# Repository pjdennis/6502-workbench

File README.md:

# 6502 workbench

Homebrew 6502 single-board computers and the software written for them: board firmware and peripheral drivers, self-hosting assemblers, a vi-like editor, a Prog8 compiler that compiles itself on the target, and a board-accurate emulator. It has grown since 2020. [`docs/history.md`](docs/history.md) tells the story and shows how to build each era.

This repository continues `pjdennis/6502-experiments`, reorganized in 2026-09 with its full history. Every commit of every old branch is here: on `main`, or, for work that was never merged, reachable from an `archive/<branch>` tag. There is one such tag for each old branch, recording where it pointed.

## Map

| Directory | What's there |
|---|---|
| [`hardware/`](hardware/) | The boards: **Wendy** (v1, 2020), **Michael** (v2, 2021) and **Wendy 2** (2022, now revision c). PLD equations, pin notes, revision history, and the Arduino monitor used with Michael. |
| [`firmware/`](firmware/) | Everything assembled with vasm for the real boards: shared libraries (`lib/`), per-board config and loaders (`boards/`), programs (`programs/`), fonts. |
| [`emulator/`](emulator/) | C emulator. `nmos-default` is a host-stub machine for the assemblers and editor. `wendy2c` models Wendy 2 rev c chip by chip (PLD, VIA, LCD, banked RAM), with web, audio and serial-link front ends. |
| [`asm/`](asm/) | The assembler, bootstrapped from nothing: `00/asm.c`, then stages `01`…`17`, each built by the one before. `17/` is the live assembler. |
| [`editor/`](editor/) | A vi-like text editor written in the assembler's dialect and built by stage 17. Runs in the emulator's terminal and on the Michael board. |
| [`prog8/`](prog8/) | Prog8 compiler work: host compiler `p8c`, `tinyp8`, the self-hosting `p1`, and custom upstream prog8c targets for Wendy 2. |
| [`lathe/`](lathe/) | Lathe, a high-level language and compiler designed to compile on a 6502. Design documents only so far. |
| [`tools/`](tools/) | Host-side tools: serial upload (`upload/`), webcam LCD OCR (`lcd-ocr/`), `makerom.py`, the firmware regression check, `check_all.sh`. |
| [`research/`](research/) | Analyses, e.g. a byte-level breakdown of BBC BASIC IV. |
| [`attic/`](attic/) | Stale, broken or superseded things kept for review, including the first assembler (`asm1/`, 2022–2025). See [`attic/README.md`](attic/README.md). |
| [`docs/`](docs/README.md) | History, the plan behind the 2026 reorganization, and the plans for Michael's ROM and upload format (both done). |

## Quick start

Prerequisites:
- `gcc`, `make` and `python3`
- **vasm** (`vasm6502_oldstyle`, CPU=6502 SYNTAX=oldstyle), on `PATH`. 1.9f to 2.0f all work; CI uses 2.0f from <http://phoenix.owl.de/tags/vasm2_0f.tar.gz>. See `firmware/README.md`.
- Optional: `hexdump`, `64tass`, Java with prog8c 12.1.1, and Python `playwright`. Tests that need a missing tool are skipped.

```bash
make                                   # build the emulator (emulator/emulator.out)
tools/build_all.sh                     # ...or the emulator, assembler and editor (about 30 seconds)
tools/check_all.sh                     # run the test suites, all but the slow prog8 (about 2 minutes)
tools/check_all.sh firmware asm        # ...or just some: firmware asm editor emulator prog8

# Assemble and upload a program to a board over serial
tools/upload/compile_and_upload_wendy2.sh firmware/programs/wendy2/hello_ram_4000_wendy2c.s

# Try Wendy 2 without the hardware
bash emulator/demo_wendy2c.sh --live
```

CI (`.github/workflows/ci.yml`) runs all five `check_all.sh` suites, prog8 included, on every push.

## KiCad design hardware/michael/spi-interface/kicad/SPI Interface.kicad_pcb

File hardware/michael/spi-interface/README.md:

# Michael: the SPI interface in logic chips (2022–2025)

The designs for the interface between Michael's VIA and the SPI display, before the FPGA, kept as found on
2026-10-25 (file dates preserved). The write-up, with the timeline and a review of each design:
[`docs/michael-spi-interface-logic-designs.md`](../../../docs/michael-spi-interface-logic-designs.md).

| Directory | What | Open with |
|---|---|---|
| [`logisim/`](logisim/) | `SPI.circ`, `SPI2.circ`, `SPI3.circ`, `299.circ` (2022-09-13 to 15) | Logisim 2.7 |
| [`digital/`](digital/) | `D-SPI.dig` and its `e-4017.dig`, `D-SPI2.dig`, `shtest.dig` (2022-09-15/16), `D-SPI-WriteOnly.dig` and its Verilog (2024-10-15); `CUPL_D-SPI2/CUPL.PLD` and `test.v`, exported by Digital (2022-09-16); an SVG of each circuit | [Digital](https://github.com/hneemann/Digital) v0.29 |
| [`kicad/`](kicad/) | "Bidirectional SPI interface" rev 0.1 in 74LS chips (2025-10-04): schematic, and a PCB with the parts placed but not routed | KiCad 6 |
| [`gal/`](gal/) | `spi-control.pld` for a GAL20RA10 and a 74HC299 (2025-10-10) and `program-spi.sh`; [`bring-up/`](gal/bring-up/), the GAL20RA10 test designs of 2025-10-04 | GALasm, minipro |

The GAL design works on Michael with a W5500 module, which answers ping (2026-10-25, after wiring faults and
signal integrity work: see the write-up's "Tried again", "Ping" and "Assessment"; the W5500 is to move to the FPGA
bus). The emulator models the GAL design and a W5500 on it (`--add gal-spi,w5500` on `--machine michael`:
`emulator/chips/gal_spi.h`, `emulator/chips/w5500.h`), and
[`michael_w5500_version.s`](../../../firmware/programs/michael/michael_w5500_version.s) reads the W5500 through it,
on the board or the emulator.

The 74LS schematic has a wiring fault (the counter's enable from the wrong flip-flop output): see the write-up.

Digital's command line runs `D-SPI2.dig`'s test and redraws the SVGs, without a display:

```
java -Djava.awt.headless=true -cp Digital.jar CLI test -circ digital/D-SPI2.dig
java -Djava.awt.headless=true -cp Digital.jar CLI svg -dig digital/D-SPI.dig -svg digital/D-SPI.svg
```

JEDEC files are build output here (`.gitignore`). `galasm gal/spi-control.pld` makes `spi-control.jed`, identical
to the one in `~/research/pld` that `program-spi.sh` programs, with `.chp`, `.fus` and `.pin` files beside it.

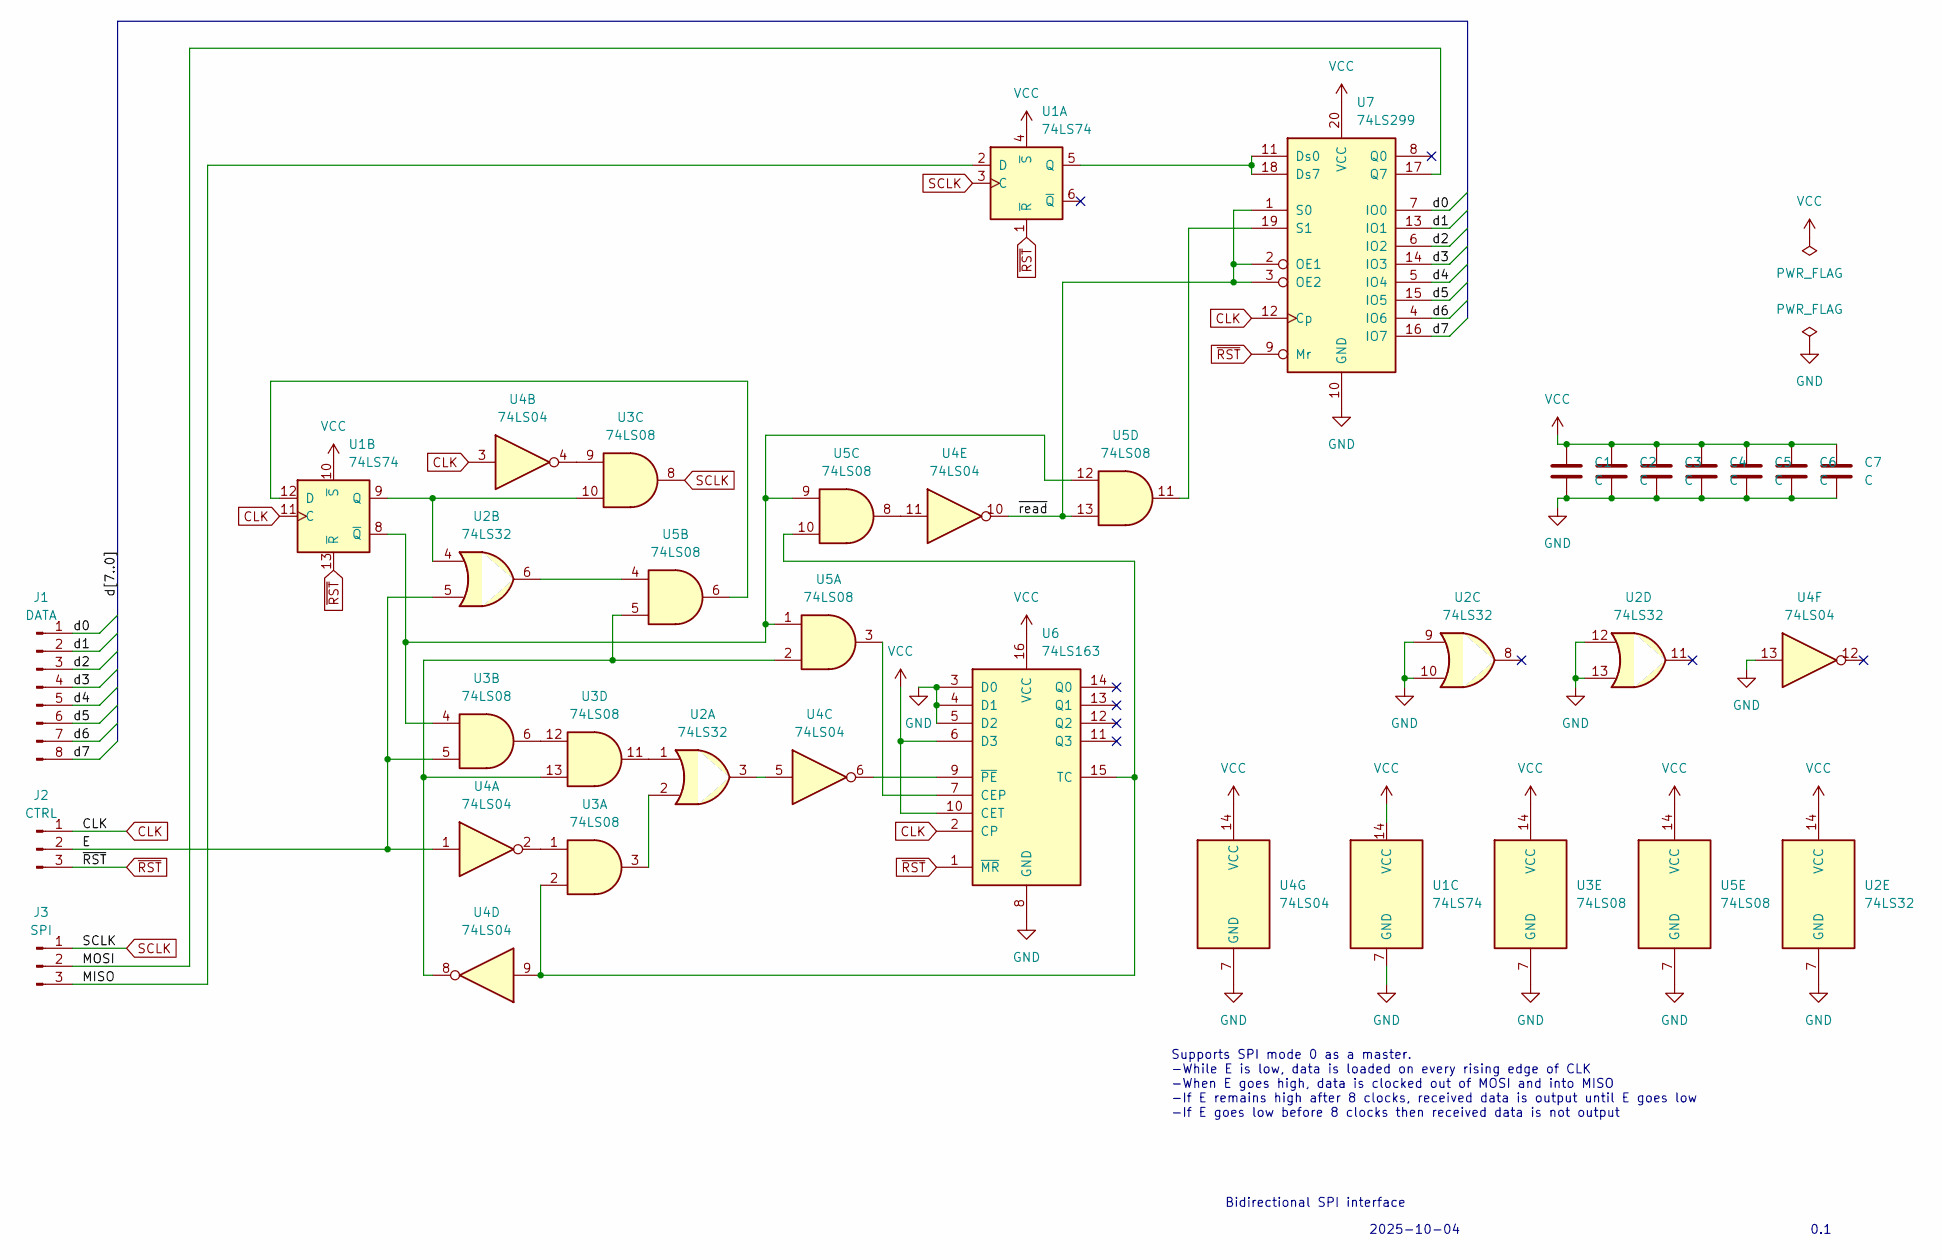
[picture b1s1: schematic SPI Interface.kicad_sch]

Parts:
C1, C2, C3, C4, C5, C6, C7: C; C_Disc_D4.3mm_W1.9mm_P5.00mm
J1: DATA; PinHeader_1x08_P2.54mm_Vertical
J2: CTRL; PinHeader_1x03_P2.54mm_Vertical
J3: SPI; PinHeader_1x03_P2.54mm_Vertical
U1: 74LS74; DIP-14_W7.62mm
U2: 74LS32; DIP-14_W7.62mm
U3, U5: 74LS08; DIP-14_W7.62mm
U4: 74LS04; DIP-14_W7.62mm
U6: 74LS163; DIP-16_W7.62mm
U7: 74LS299; DIP-20_W7.62mm

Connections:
/E: J2.2, U2.5, U3.5, U4.1
/MISO: J3.3, U1.2 (D)
/MOSI: J3.2, U7.17 (Q7)
/d0: J1.1, U7.7 (IO0)
/d1: J1.2, U7.13 (IO1)
/d2: J1.3, U7.6 (IO2)
/d3: J1.4, U7.14 (IO3)
/d4: J1.5, U7.5 (IO4)
/d5: J1.6, U7.15 (IO5)
/d6: J1.7, U7.4 (IO6)
/d7: J1.8, U7.16 (IO7)
/~read: U4.10, U5.13, U7.1 (S0), U7.2 (OE1), U7.3 (OE2)
CLK: J2.1, U1.11 (C), U4.3, U6.2 (CP), U7.12 (Cp)
GND: C1.2, C2.2, C3.2, C4.2, C5.2, C6.2, C7.2, U1.7 (GND), U2.7 (GND), U2.9, U2.10, U2.12, U2.13, U3.7 (GND), U4.7 (GND), U4.13, U5.7 (GND), U6.3 (D0), U6.4 (D1), U6.5 (D2), U6.8 (GND), U7.10 (GND)
unnamed: U1.5 (Q), U7.11 (Ds0), U7.18 (Ds7)
unnamed: U1.8 (~Q), U3.4, U5.1, U5.9, U5.12
unnamed: U1.9 (Q), U2.4, U3.10
unnamed: U1.12 (D), U5.6
unnamed: U2.1, U3.11
unnamed: U2.2, U3.3
unnamed: U2.3, U4.5
unnamed: U2.6, U5.4
unnamed: U3.1, U4.2
unnamed: U3.2, U4.9, U5.10, U6.15 (TC)
unnamed: U3.9, U4.4
unnamed: U3.6, U3.12
unnamed: U3.13, U4.8, U5.2, U5.5
unnamed: U4.6, U6.9 (~PE)
unnamed: U4.11, U5.8
unnamed: U5.3, U6.7 (CEP)
unnamed: U5.11, U7.19 (S1)
SCLK: J3.1, U1.3 (C), U3.8
VCC: C1.1, C2.1, C3.1, C4.1, C5.1, C6.1, C7.1, U1.4 (~S), U1.10 (~S), U1.14 (VCC), U2.14 (VCC), U3.14 (VCC), U4.14 (VCC), U5.14 (VCC), U6.6 (D3), U6.10 (CET), U6.16 (VCC), U7.20 (VCC)
~RST: J2.3, U1.1 (~R), U1.13 (~R), U6.1 (~MR), U7.9 (Mr)

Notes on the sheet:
Bidirectional SPI interface
2025-10-04
Supports SPI mode 0 as a master. -While E is low, data is loaded on every rising edge of CLK -When E goes high, data is clocked out of MOSI and into MISO -If E remains high after 8 clocks, received data is output until E goes low -If E goes low before 8 clocks then received data is not output
0.1

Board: 2 copper layers, 17 parts (0 on the bottom side), 34 nets, no tracks yet.
